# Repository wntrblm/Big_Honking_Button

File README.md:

# Winterbloom Big Honking Button

Winterbloom Big Honking Button is an open-source Eurorack module. You can find out more at https://honk.wntr.dev/.

## License and contributing

The code here is available under the [MIT License](firmware/LICENSE), the hardware designs are available under [CC BY-SA 4.0](hardware/LICENSE). I welcome contributors, please read the [Code of Conduct](CODE_OF_CONDUCT.md) first. :)

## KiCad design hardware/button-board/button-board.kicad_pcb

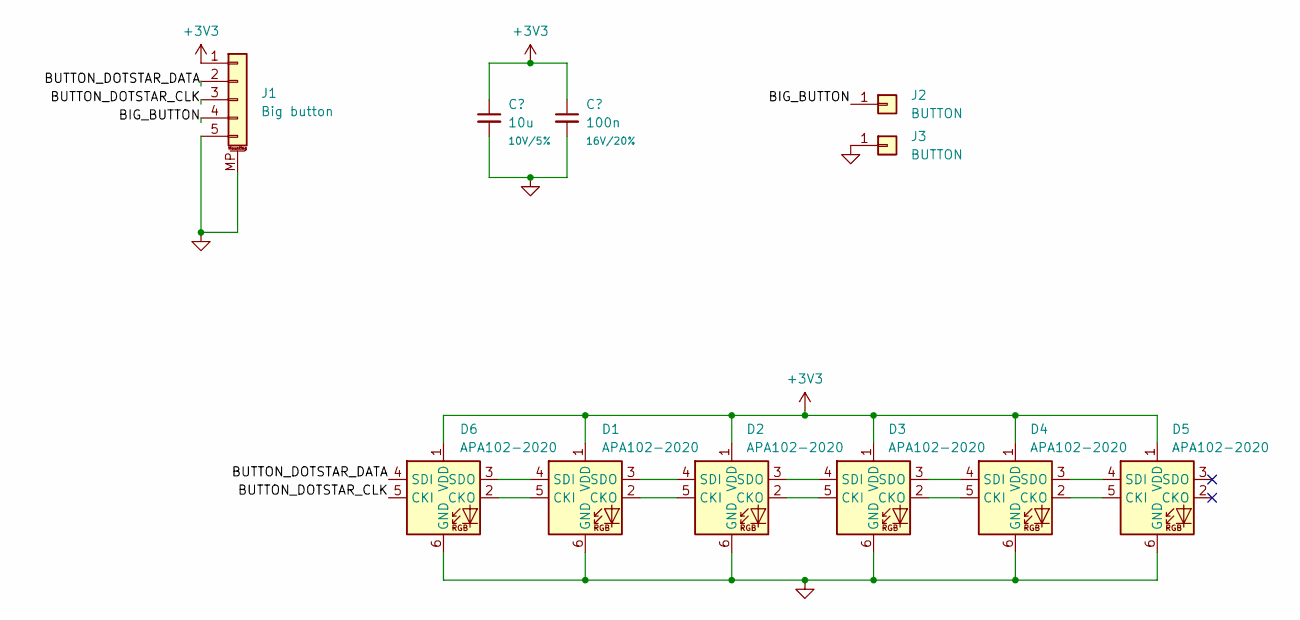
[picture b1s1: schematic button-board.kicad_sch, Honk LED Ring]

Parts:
C1: 10u; C_0603_HandSolder; Rating 10V/5%; MPN CL10A106MP8NNNC
C2: 100n; C_0603_HandSolder; Rating 16V/20%; MPN CL05B104KO5NNNC
D1, D2, D3, D4, D5, D6: APA102-2020; LED-APA102-2020; MPN APA102-2020
J1: Big button; JST_SH_SM05B-SRSS-TB_1x05-1MP_P1.00mm_Horizontal
J2, J3: BUTTON; SolderWire-0.75sqmm_1x01_D1.25mm_OD2.3mm

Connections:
+3V3: C1.1, C2.1, D1.1 (VDD), D2.1 (VDD), D3.1 (VDD), D4.1 (VDD), D5.1 (VDD), D6.1 (VDD), J1.1
/BIG_BUTTON: J1.4, J2.1
/BUTTON_DOTSTAR_CLK: D6.5 (CKI), J1.3
/BUTTON_DOTSTAR_DATA: D6.4 (SDI), J1.2
GND: C1.2, C2.2, D1.6 (GND), D2.6 (GND), D3.6 (GND), D4.6 (GND), D5.6 (GND), D6.6 (GND), J1.5, J1.MP (MountPin), J3.1
unnamed: D1.5 (CKI), D6.2 (CKO)
unnamed: D1.2 (CKO), D2.5 (CKI)
unnamed: D1.4 (SDI), D6.3 (SDO)
unnamed: D1.3 (SDO), D2.4 (SDI)
unnamed: D2.2 (CKO), D3.5 (CKI)
unnamed: D2.3 (SDO), D3.4 (SDI)
unnamed: D3.2 (CKO), D4.5 (CKI)
unnamed: D3.3 (SDO), D4.4 (SDI)
unnamed: D4.2 (CKO), D5.5 (CKI)
unnamed: D4.3 (SDO), D5.4 (SDI)

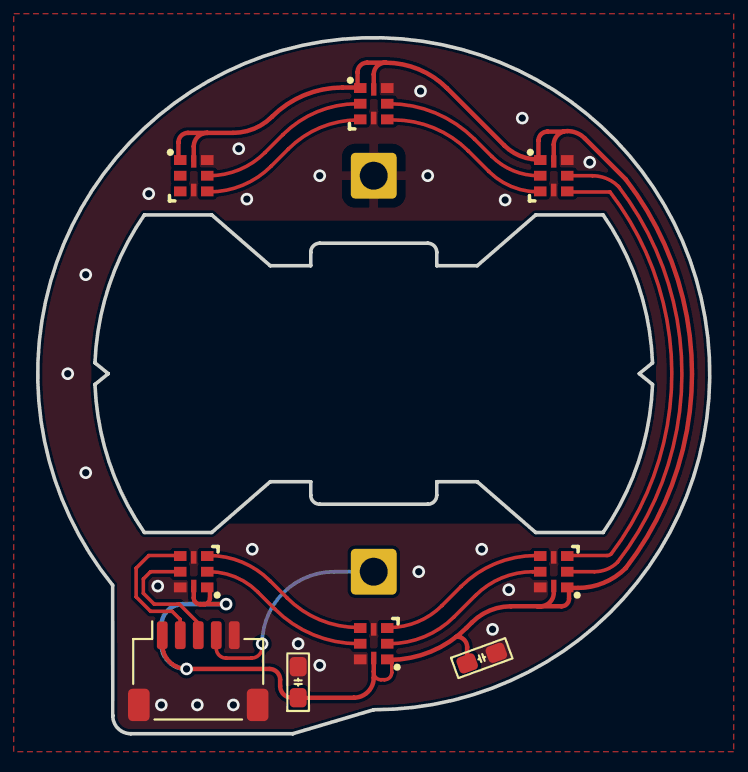
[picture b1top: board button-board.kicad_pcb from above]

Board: 2 copper layers, 37.3 x 38.7 mm, 11 parts (0 on the bottom side), 15 nets.

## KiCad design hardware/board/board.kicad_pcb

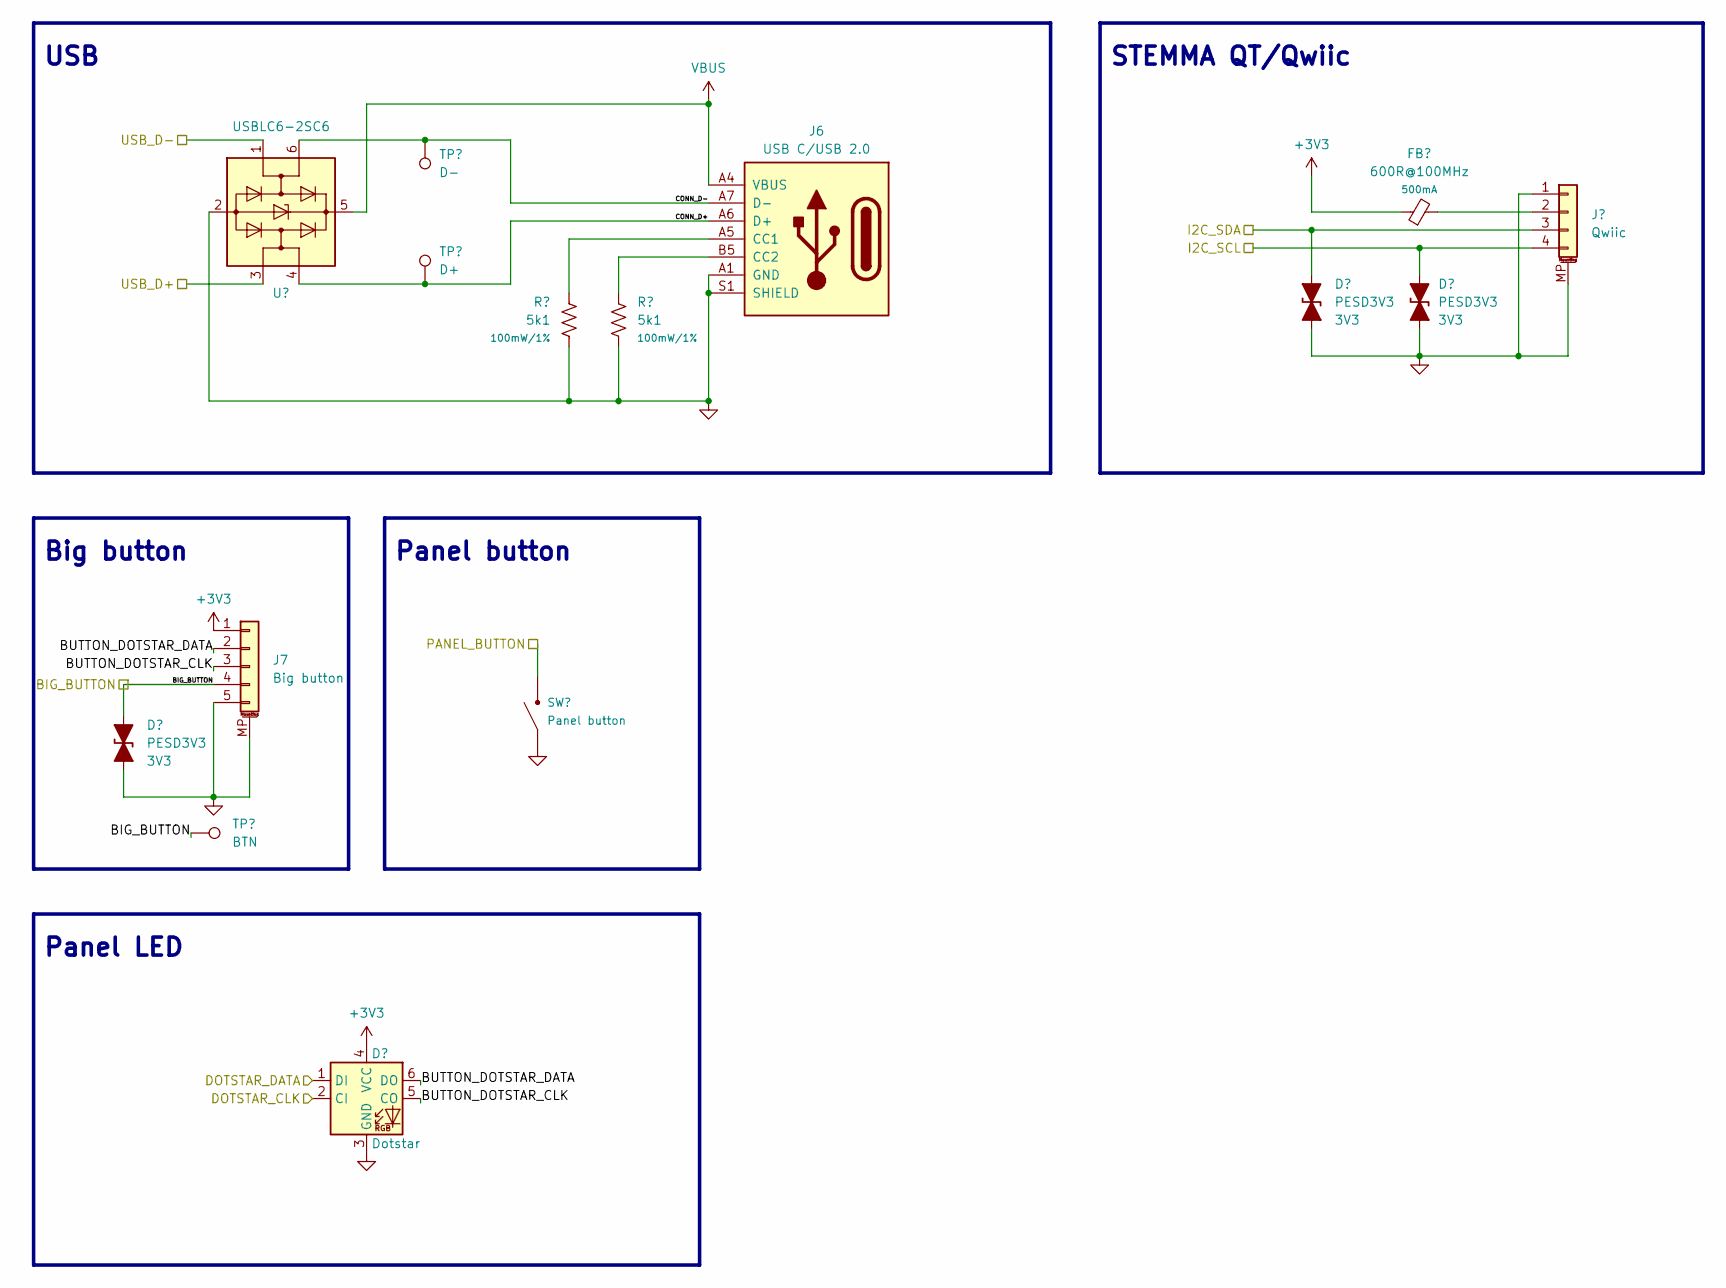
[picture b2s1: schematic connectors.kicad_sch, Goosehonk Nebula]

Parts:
D6: Dotstar; LED_APA102_Dotstar_5050; MPN SK9822
D7, D8, D9: PESD3V3; D_SOD-323; Rating 3V3; mpn PESD3V3L1BA,115
FB4: 600R@100MHz; L_0603_HandSolder; Rating 500mA; MPN 742792651
J6: USB C/USB 2.0; USB_C_Vertical_GT-USB-7038X; MPN GT-USB-7038D, MC-110LD-L124, GT-USB-703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
J7: Big button; JST_SH_SM05B-SRSS-TB_1x05-1MP_P1.00mm_Horizontal
J9: Qwiic; JST_SH_SM04B-SRSS-TB_1x04-1MP_P1.00mm_Horizontal
R23, R24: 5k1; R_0603_HandSolder; Rating 100mW/1%; MPN ERJ-2RKF2201X
SW2: Panel button; Tactile_Switch_6mm; MPN TL1105SPF160Q, TL1105SPF100Q, TL1105SPF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
TP15: D-; TestPoint_Pad_D1.0mm
TP16: D+; TestPoint_Pad_D1.0mm
TP17: BTN; TestPoint_Pad_D1.0mm
U7: USBLC6-2SC6; SOT-23-6; MPN USBLC6-2SC6, SRL05-TP

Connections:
+3V3: D6.4 (VCC), FB4.1, J7.1; also elsewhere on the board
/Connectors & buttons/BIG_BUTTON: D9.2 (A2), J7.4, TP17.1; also elsewhere on the board
/Connectors & buttons/BUTTON_DOTSTAR_CLK: D6.5 (CO), J7.3
/Connectors & buttons/BUTTON_DOTSTAR_DATA: D6.6 (DO), J7.2
/Connectors & buttons/CONN_D+: J6.A6 (D+), J6.B6 (D+), TP16.1, U7.4 (I/O2)
/Connectors & buttons/CONN_D-: J6.A7 (D-), J6.B7 (D-), TP15.1, U7.6 (I/O1)
/Connectors & buttons/DOTSTAR_CLK: D6.2 (CI); also elsewhere on the board
/Connectors & buttons/DOTSTAR_DATA: D6.1 (DI); also elsewhere on the board
/Connectors & buttons/PANEL_BUTTON: SW2.2; also elsewhere on the board
/Connectors & buttons/USB_D+: U7.3 (I/O2); also elsewhere on the board
/Connectors & buttons/USB_D-: U7.1 (I/O1); also elsewhere on the board
/MCU/I2C_SCL: D8.2 (A2), J9.4; also elsewhere on the board
/MCU/I2C_SDA: D7.2 (A2), J9.3; also elsewhere on the board
GND: D6.3 (GND), D7.1 (A1), D8.1 (A1), D9.1 (A1), J6.A1 (GND), J6.A12 (GND), J6.B1 (GND), J6.B12 (GND), J6.S1 (SHIELD), J7.5, J7.MP (MountPin), J9.1, J9.MP (MountPin), R23.2, R24.2, SW2.1, U7.2 (GND); also elsewhere on the board
unnamed: J6.A5 (CC1), R23.1
unnamed: J6.B5 (CC2), R24.1
unnamed: FB4.2, J9.2
VBUS: J6.A4 (VBUS), J6.A9 (VBUS), J6.B4 (VBUS), J6.B9 (VBUS), U7.5 (VBUS); also elsewhere on the board

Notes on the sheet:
USB
Panel button
Panel LED
STEMMA QT/Qwiic
Big button

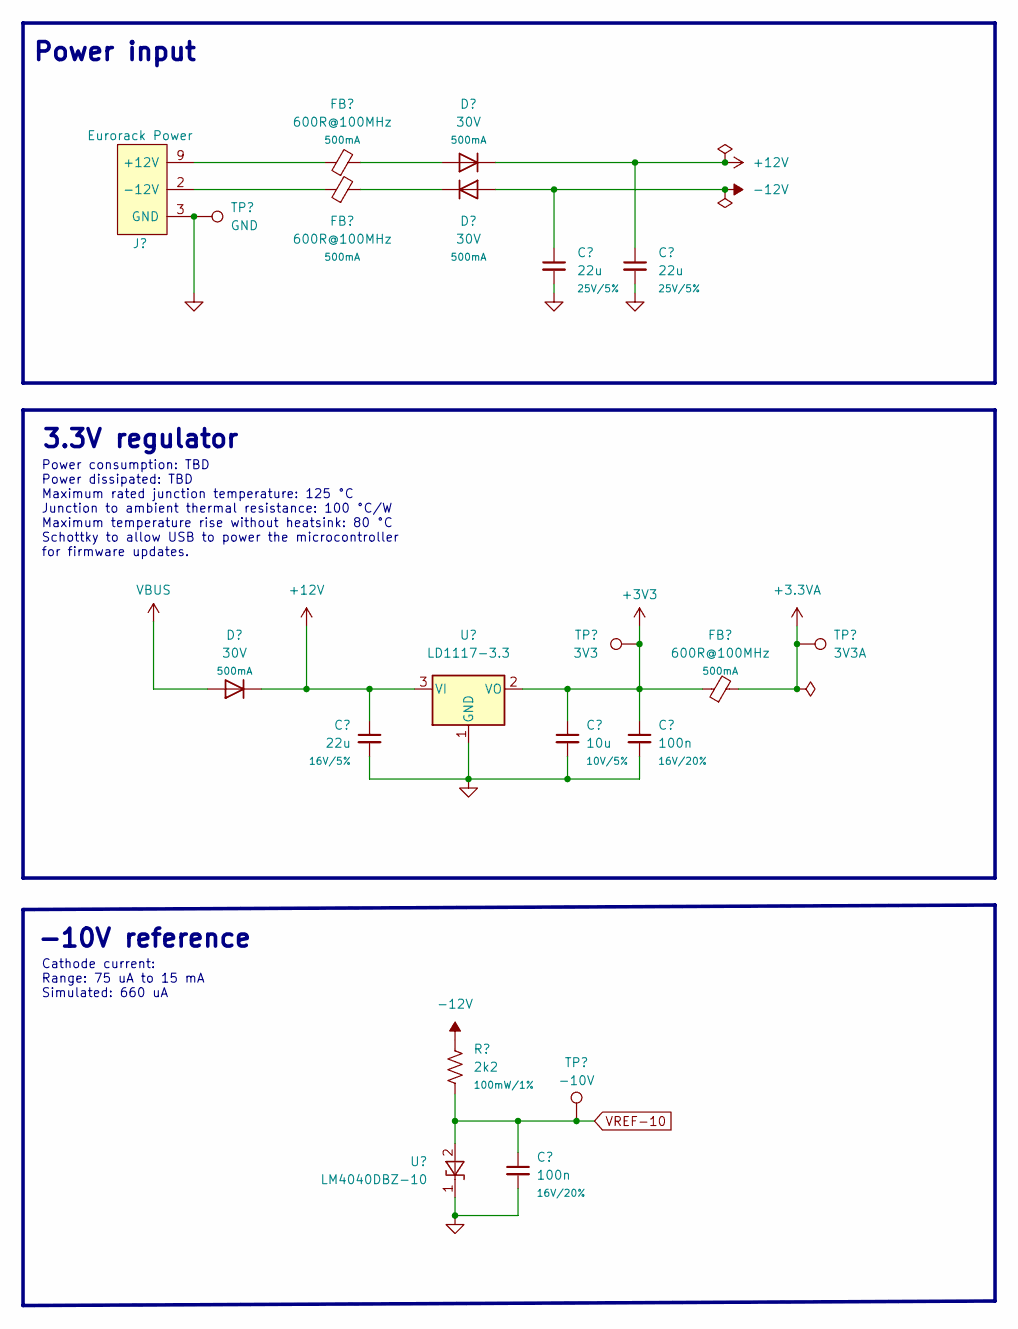
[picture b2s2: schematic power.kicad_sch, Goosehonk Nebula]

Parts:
C1, C2: 22u; C_0805_HandSolder; Rating 25V/5%; MPN CL21A226MAYNNNE
C5: 22u; C_0805_HandSolder; Rating 16V/5%; MPN CL21A226MAYNNNE
C6: 10u; C_0603_HandSolder; Rating 10V/5%; MPN CL10A106MP8NNNC
C7, C8: 100n; C_0603_HandSolder; Rating 16V/20%; MPN CL05B104KO5NNNC
D1, D2, D3: 30V; D_SOD-123; Rating 500mA; MPN PMEG2005EGWJ, PMEG3005EGWX
FB1, FB2, FB3: 600R@100MHz; L_0603_HandSolder; Rating 500mA; MPN 742792651
J1: Eurorack Power; Eurorack_Power_2x5_Shrouded_Lock; MPN 4UCONN 20253, On-shore 302-S101
R1: 2k2; R_0603_HandSolder; Rating 100mW/1%; MPN ERJ-2RKF2201X
TP1: GND; TestPoint_Pad_D1.0mm
TP2: 3V3; TestPoint_Pad_D1.0mm
TP3: 3V3A; TestPoint_Pad_D1.0mm
TP4: -10V; TestPoint_Pad_D1.0mm
U1: LD1117-3.3; TO-252-3_TabPin2; MPN LD1117DT33TR, AZ1117CD-3.3TRG1
U2: LM4040DBZ-10; SOT-23; MPN LM4040DIM3-10.0/NOPB

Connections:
+3.3VA: FB3.2, TP3.1; also elsewhere on the board
+3V3: C6.1, C7.1, FB3.1, TP2.1, U1.2 (VO); also elsewhere on the board
+12V: C2.1, C5.1, D1.1 (K), D3.1 (K), U1.3 (VI); also elsewhere on the board
-12V: C1.1, D2.2 (A), R1.1; also elsewhere on the board
GND: C1.2, C2.2, C5.2, C6.2, C7.2, C8.2, J1.3 (GND), J1.4 (GND), J1.5 (GND), J1.6 (GND), J1.7 (GND), J1.8 (GND), TP1.1, U1.1 (GND), U2.1 (K); also elsewhere on the board
unnamed: D1.2 (A), FB1.2
unnamed: D2.1 (K), FB2.2
unnamed: FB1.1, J1.9 (+12V), J1.10 (+12V)
unnamed: FB2.1, J1.1 (-12V), J1.2 (-12V)
VBUS: D3.2 (A); also elsewhere on the board
VREF-10: C8.1, R1.2, TP4.1, U2.2 (A); also elsewhere on the board

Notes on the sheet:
-10V reference
Power consumption: TBD Power dissipated: TBD Maximum rated junction temperature: 125 °C Junction to ambient thermal resistance: 100 °C/W Maximum temperature rise without heatsink: 80 °C Schottky to allow USB to power the microcontroller for firmware updates.
3.3V regulator
Cathode current: Range: 75 uA to 15 mA Simulated: 660 uA
Power input

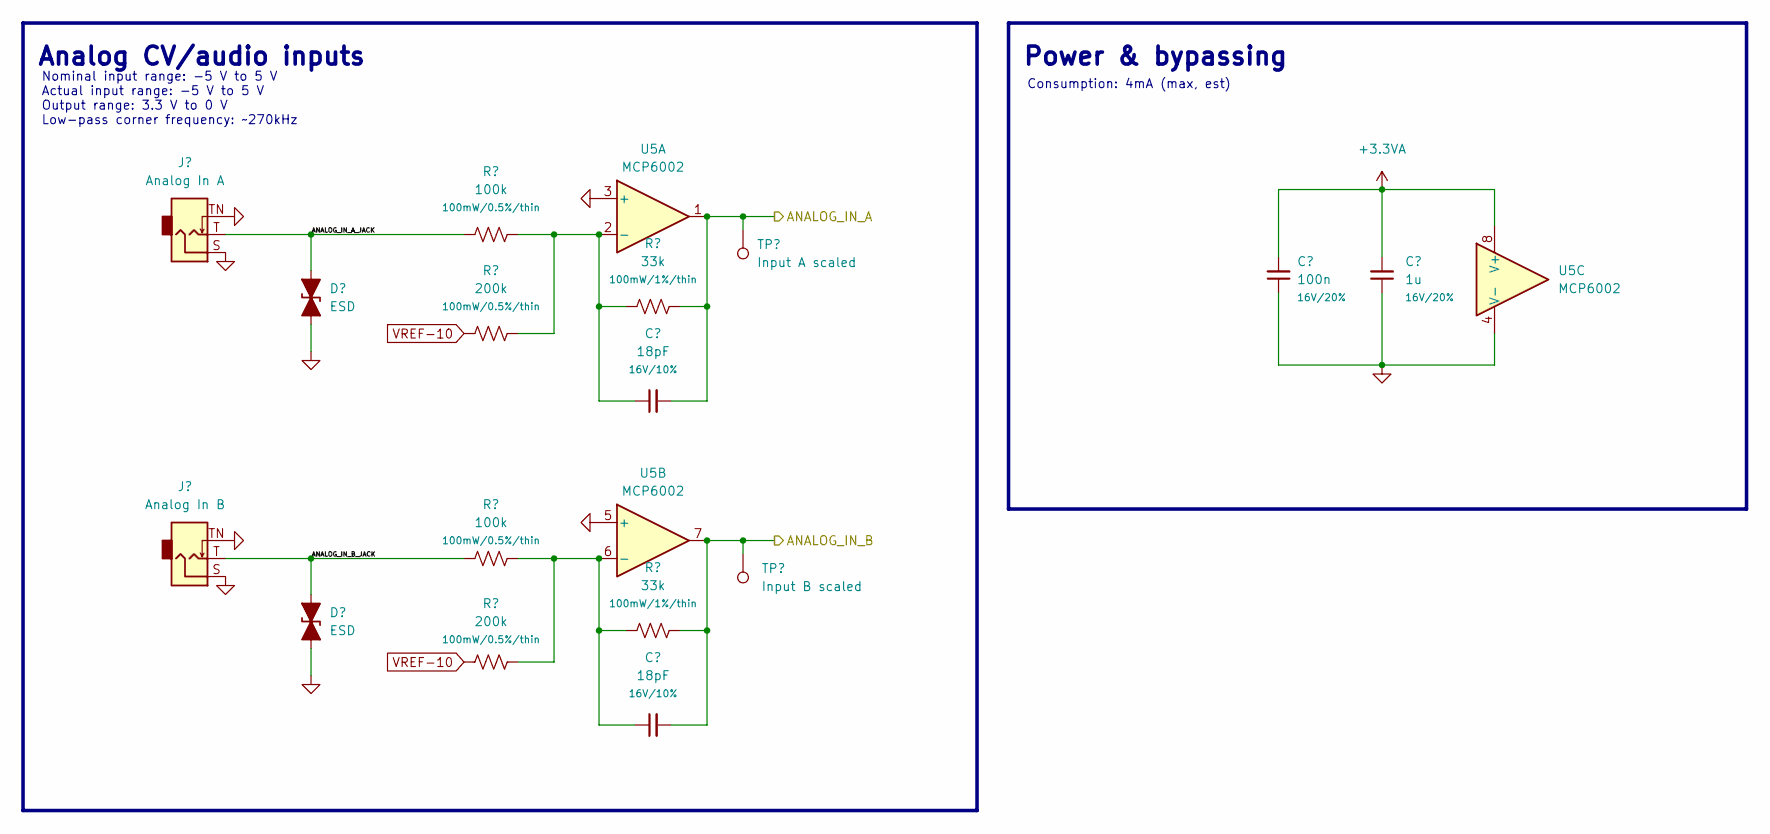
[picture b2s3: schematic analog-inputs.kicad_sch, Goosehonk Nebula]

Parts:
C16, C17: 18pF; C_0603_HandSolder; Rating 16V/10%; MPN GRM155R71H222KA01D
C18: 100n; C_0603_HandSolder; Rating 16V/20%; MPN CL05B104KO5NNNC
C19: 1u; C_0603_HandSolder; Rating 16V/20%; MPN CL05A105KO5NNNC
D4, D5: ESD; C_0603_HandSolder; Rating 20V+; MPN B72500T0250K060
J2: Analog In A; AudioJack_WQP518MA; MPN WQP-WQP518MA
J3: Analog In B; AudioJack_WQP518MA; MPN WQP-WQP518MA
R5, R8: 100k; R_0603_HandSolder; Rating 100mW/0.5%/thin; MPN RC0402DR-07100KL
R6, R9: 200k; R_0603_HandSolder; Rating 100mW/0.5%/thin; MPN RP73PF1E196KBTD, RK73H1ETTP1963F
R7, R10: 33k; R_0603_HandSolder; Rating 100mW/1%/thin; MPN RT0402BRD0761K9L, ERA-2AEB6192X
TP10: Input A scaled; TestPoint_Pad_D1.0mm
TP11: Input B scaled; TestPoint_Pad_D1.0mm
U5: MCP6002; MSOP-8_3x3mm_P0.65mm; MPN MCP6002T-I/MS, MCP6002-I/MS, MCP6002T-E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

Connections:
+3.3VA: C18.2, C19.2, U5.8 (V+); also elsewhere on the board
/Analog Inputs/ANALOG_IN_A: C16.2, R7.1, TP10.1, U5.1; also elsewhere on the board
/Analog Inputs/ANALOG_IN_A_JACK: D4.2 (A2), J2.T (Tip), R5.2
/Analog Inputs/ANALOG_IN_B: C17.2, R10.1, TP11.1, U5.7; also elsewhere on the board
/Analog Inputs/ANALOG_IN_B_JACK: D5.2 (A2), J3.T (Tip), R8.2
GND: C18.1, C19.1, D4.1 (A1), D5.1 (A1), J2.S (Sleeve), J2.TN (Tip_normalize), J3.S (Sleeve), J3.TN (Tip_normalize), U5.3 (+), U5.4 (V-), U5.5 (+); also elsewhere on the board
unnamed: C16.1, R5.1, R6.1, R7.2, U5.2 (-)
unnamed: C17.1, R8.1, R9.1, R10.2, U5.6 (-)
VREF-10: R6.2, R9.2; also elsewhere on the board

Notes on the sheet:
Nominal input range: -5 V to 5 V Actual input range: -5 V to 5 V Output range: 3.3 V to 0 V Low-pass corner frequency: ~270kHz
Consumption: 4mA (max, est)
Analog CV/audio inputs
Power & bypassing

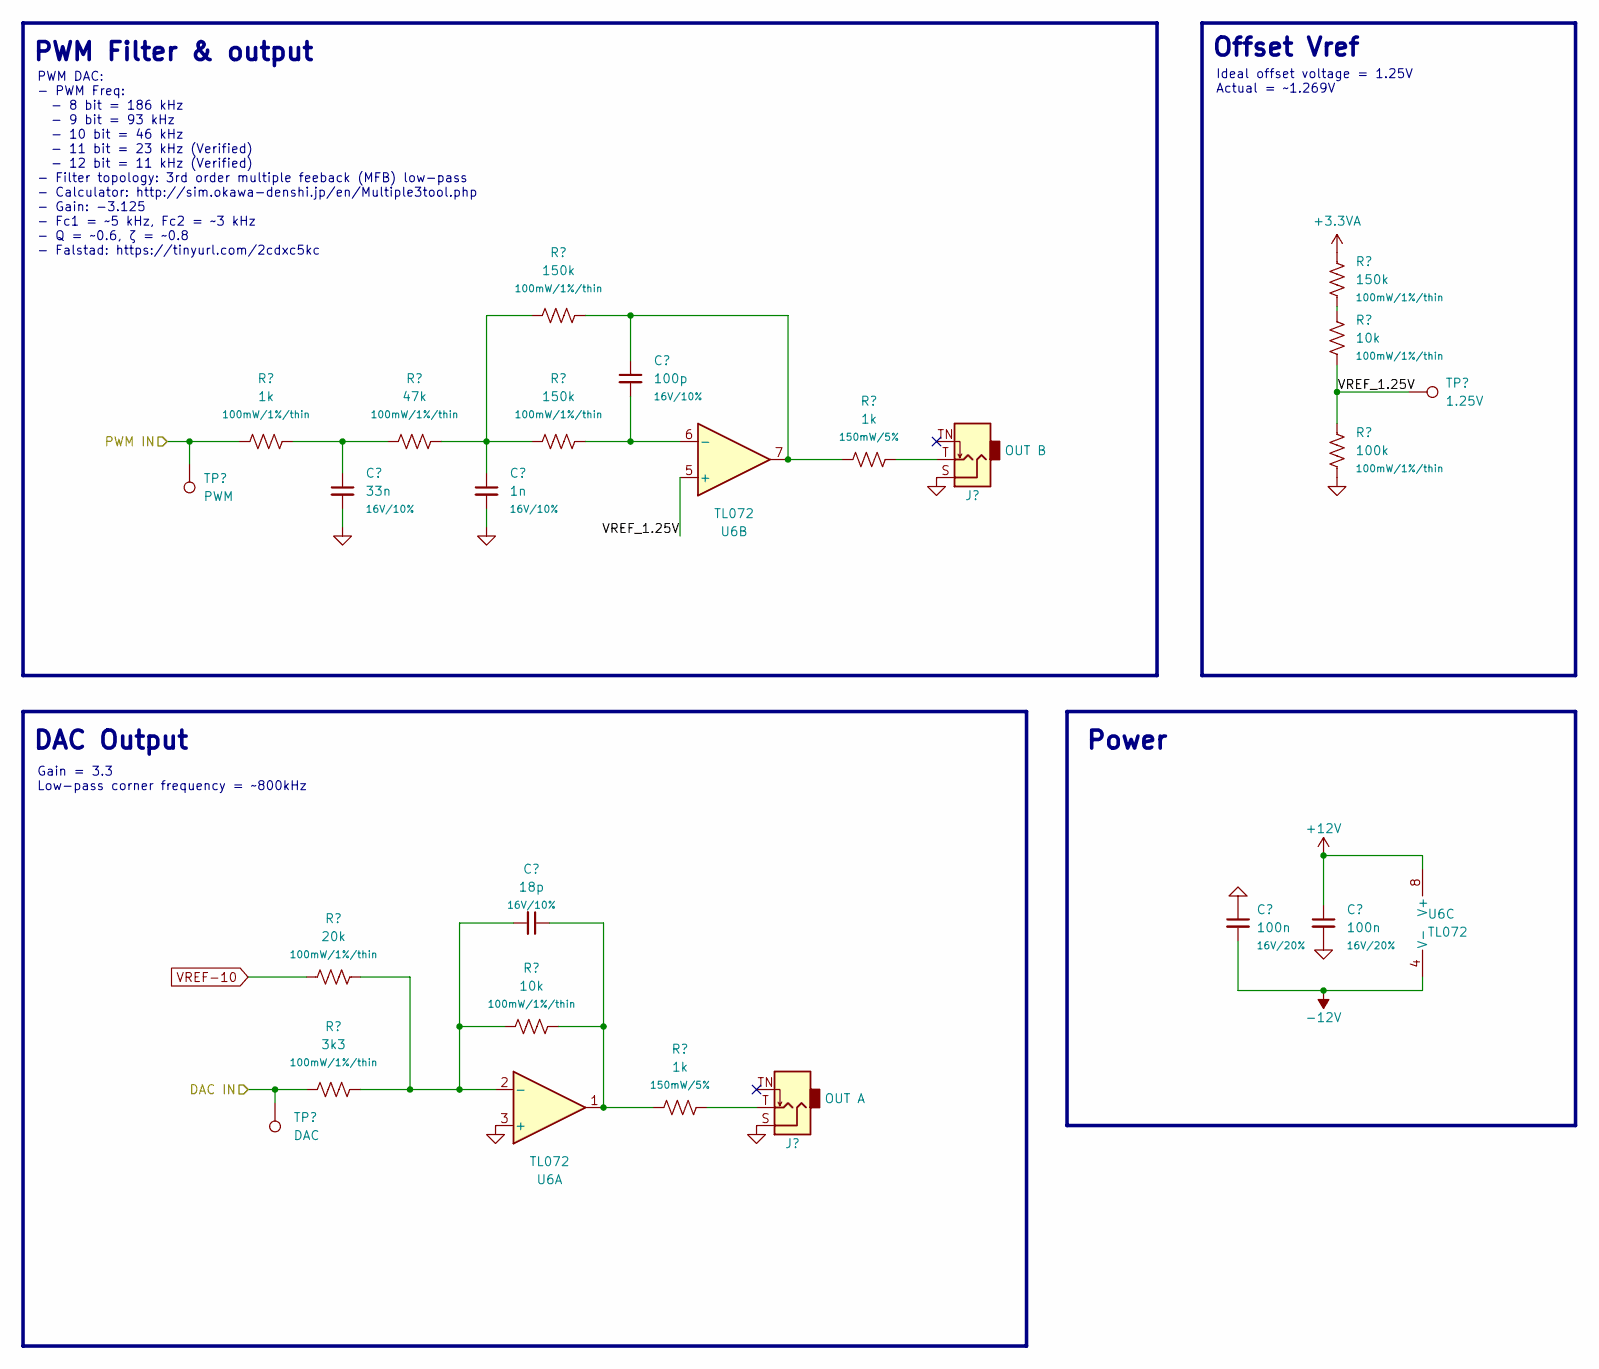
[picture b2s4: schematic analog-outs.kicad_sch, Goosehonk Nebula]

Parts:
C20, C21: 100n; C_0603_HandSolder; Rating 16V/20%; MPN CL05B104KO5NNNC
C22: 18p; C_0603_HandSolder; Rating 16V/10%; MPN CL05C180JB5NNNC
C23: 33n; C_0603_HandSolder; Rating 16V/10%; MPN CL05C180JB5NNNC
C24: 1n; C_0603_HandSolder; Rating 16V/10%; MPN CL05C180JB5NNNC
C25: 100p; C_0603_HandSolder; Rating 16V/10%; MPN CL05C180JB5NNNC
J4: OUT A; AudioJack_WQP518MA; MPN WQP-WQP518MA
J5: OUT B; AudioJack_WQP518MA; MPN WQP-WQP518MA
R11: 20k; R_0603_HandSolder; Rating 100mW/1%/thin; MPN RC0402DR-07100KL
R12: 3k3; R_0603_HandSolder; Rating 100mW/1%/thin; MPN RC0402DR-07100KL
R13, R21: 10k; R_0603_HandSolder; Rating 100mW/1%/thin; MPN RC0402DR-07100KL
R14, R19: 1k; R_0603_HandSolder; Rating 150mW/5%; MPN MCT06030C1001FP500, ERA-3AEB102V
R15: 1k; R_0603_HandSolder; Rating 100mW/1%/thin; MPN RC0402DR-07100KL
R16: 47k; R_0603_HandSolder; Rating 100mW/1%/thin; MPN RC0402DR-07100KL
R17, R18, R20: 150k; R_0603_HandSolder; Rating 100mW/1%/thin; MPN RC0402DR-07100KL
R22: 100k; R_0603_HandSolder; Rating 100mW/1%/thin; MPN RC0402DR-07100KL
TP12: DAC; TestPoint_Pad_D1.0mm
TP13: PWM; TestPoint_Pad_D1.0mm
TP14: 1.25V; TestPoint_Pad_D1.0mm
U6: TL072; TSSOP-8_4.4x3mm_P0.65mm

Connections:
+3.3VA: R20.1; also elsewhere on the board
+12V: C21.1, U6.8 (V+); also elsewhere on the board
-12V: C20.2, U6.4 (V-); also elsewhere on the board
/Analog Outs/DAC IN: R12.2, TP12.1; also elsewhere on the board
/Analog Outs/PWM IN: R15.2, TP13.1; also elsewhere on the board
/Analog Outs/VREF_1.25V: R21.2, R22.1, TP14.1, U6.5 (+)
GND: C20.1, C21.2, C23.2, C24.2, J4.S (Sleeve), J5.S (Sleeve), R22.2, U6.3 (+); also elsewhere on the board
unnamed: C22.1, R13.1, R14.1, U6.1
unnamed: C23.1, R15.1, R16.2
unnamed: C24.1, R16.1, R17.2, R18.2
unnamed: C25.1, R17.1, R19.1, U6.7
unnamed: J4.T (Tip), R14.2
unnamed: J5.T (Tip), R19.2
unnamed: R20.2, R21.1
unnamed: C22.2, R11.1, R12.1, R13.2, U6.2 (-)
unnamed: C25.2, R18.1, U6.6 (-)
VREF-10: R11.2; also elsewhere on the board

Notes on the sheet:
Ideal offset voltage = 1.25V Actual = ~1.269V
Gain = 3.3 Low-pass corner frequency = ~800kHz
Offset Vref
PWM Filter & output
DAC Output
Power
PWM DAC: - PWM Freq: - 8 bit = 186 kHz - 9 bit = 93 kHz - 10 bit = 46 kHz - 11 bit = 23 kHz (Verified) - 12 bit = 11 kHz (Verified) - Filter topology: 3rd order multiple feeback (MFB) low-pass - Calculator: http://sim.okawa-denshi.jp/en/Multiple3tool.php - Gain: -3.125 - Fc1 = ~5 kHz, Fc2 = ~3 kHz 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

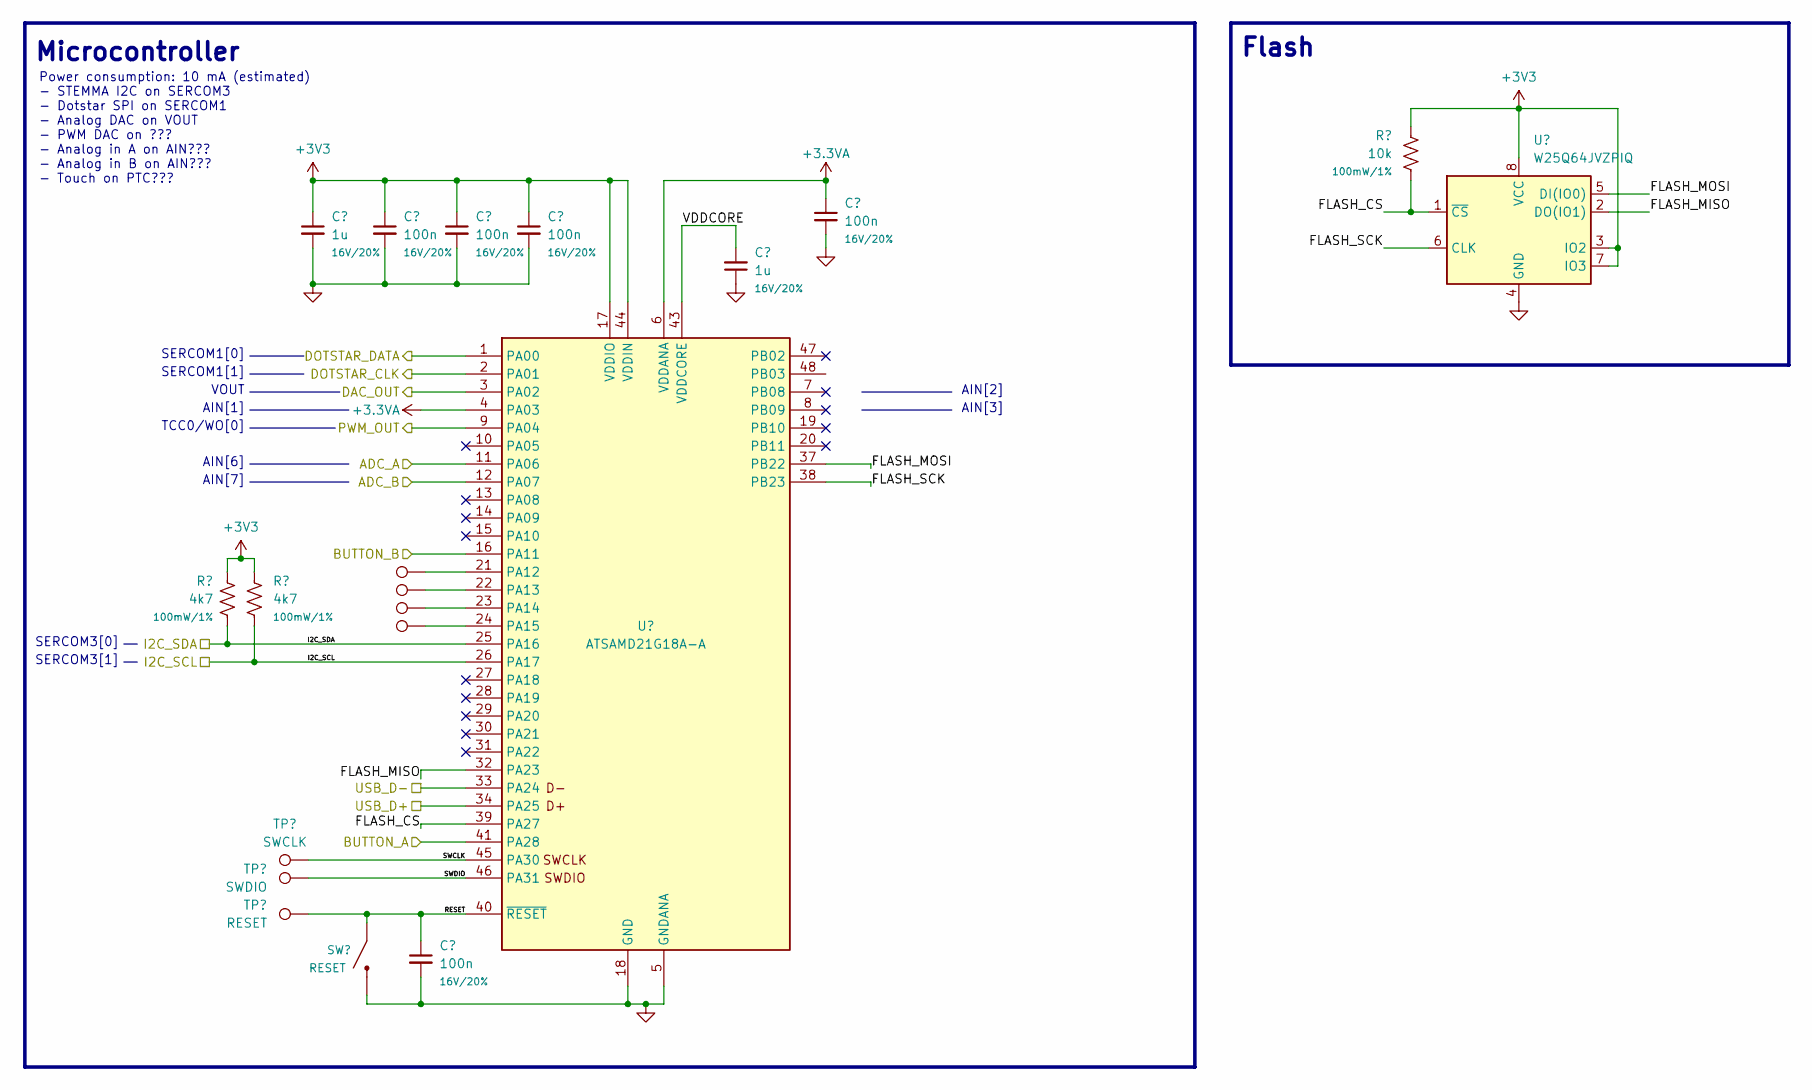
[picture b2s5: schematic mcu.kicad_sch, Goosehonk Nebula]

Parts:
C9, C14: 1u; C_0603_HandSolder; Rating 16V/20%; MPN CL05A105KO5NNNC
C10, C11, C12, C13, C15: 100n; C_0603_HandSolder; Rating 16V/20%; MPN CL05B104KO5NNNC
R2, R3: 4k7; R_0603_HandSolder; Rating 100mW/1%
R4: 10k; R_0603_HandSolder; Rating 100mW/1%; MPN ERJ-2RKF2201X
SW1: RESET; Tactile_Switch_4.2mm; MPN PTS815 SJM 250 SMTR LFS
TP7: SWCLK; TestPoint_Pad_D1.0mm
TP8: SWDIO; TestPoint_Pad_D1.0mm
TP9: RESET; TestPoint_Pad_D1.0mm
TP18: PA12; TestPoint_Pad_D1.0mm
TP19, TP20: PA13; TestPoint_Pad_D1.0mm
TP21: PA15; TestPoint_Pad_D1.0mm
U3: ATSAMD21G18A-A; TQFP-48_7x7mm_P0.5mm; MPN ATSAMD21G18A-A
U4: W25Q64JVZPIQ; WSON-8-1EP_6x5mm_P1.27mm_EP3.4x4mm; mpn W25Q64JVZPIQ

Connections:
+3.3VA: C15.1, U3.4 (PA03), U3.6 (VDDANA); also elsewhere on the board
+3V3: C9.1, C10.1, C12.1, C13.1, R2.1, R3.1, R4.1, U3.17 (VDDIO), U3.36 (VDDIO), U3.44 (VDDIN), U4.3 (IO2), U4.7 (IO3), U4.8 (VCC); also elsewhere on the board
/Analog Inputs/ANALOG_IN_A: U3.11 (PA06); also elsewhere on the board
/Analog Inputs/ANALOG_IN_B: U3.12 (PA07); also elsewhere on the board
/Analog Outs/DAC IN: U3.3 (PA02); also elsewhere on the board
/Analog Outs/PWM IN: U3.9 (PA04); also elsewhere on the board
/Connectors & buttons/BIG_BUTTON: U3.41 (PA28); also elsewhere on the board
/Connectors & buttons/DOTSTAR_CLK: U3.2 (PA01); also elsewhere on the board
/Connectors & buttons/DOTSTAR_DATA: U3.1 (PA00); also elsewhere on the board
/Connectors & buttons/PANEL_BUTTON: U3.16 (PA11); also elsewhere on the board
/Connectors & buttons/USB_D+: U3.34 (PA25); also elsewhere on the board
/Connectors & buttons/USB_D-: U3.33 (PA24); also elsewhere on the board
/MCU/FLASH_CS: R4.2, U3.39 (PA27), U4.1 (~CS)
/MCU/FLASH_MISO: U3.32 (PA23), U4.2 (DO(IO1))
/MCU/FLASH_MOSI: U3.37 (PB22), U4.5 (DI(IO0))
/MCU/FLASH_SCK: U3.38 (PB23), U4.6 (CLK)
/MCU/I2C_SCL: R3.2, U3.26 (PA17); also elsewhere on the board
/MCU/I2C_SDA: R2.2, U3.25 (PA16); also elsewhere on the board
/MCU/RESET: C11.1, SW1.1, TP9.1, U3.40 (~RESET)
/MCU/SWCLK: TP7.1, U3.45 (PA30)
/MCU/SWDIO: TP8.1, U3.46 (PA31)
/MCU/VDDCORE: C14.2, U3.43 (VDDCORE)
GND: C9.2, C10.2, C11.2, C12.2, C13.2, C14.1, C15.2, SW1.2, U3.5 (GNDANA), U3.18 (GND), U3.35 (GND), U3.42 (GND), U4.4 (GND); also elsewhere on the board
unnamed: TP18.1, U3.21 (PA12)
unnamed: TP19.1, U3.22 (PA13)
unnamed: TP20.1, U3.23 (PA14)
unnamed: TP21.1, U3.24 (PA15)

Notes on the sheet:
Microcontroller
SERCOM3[0]
TCC0/WO[0]
SERCOM3[1]
SERCOM1[1]
AIN[7]
AIN[6]
AIN[3]
Power consumption: 10 mA (estimated) - STEMMA I2C on SERCOM3 - Dotstar SPI on SERCOM1 - Analog DAC on VOUT - PWM DAC on ??? - Analog in A on AIN??? - Analog in B on AIN??? - Touch on PTC???
AIN[2]
VOUT
AIN[1]
SERCOM1[0]
Flash

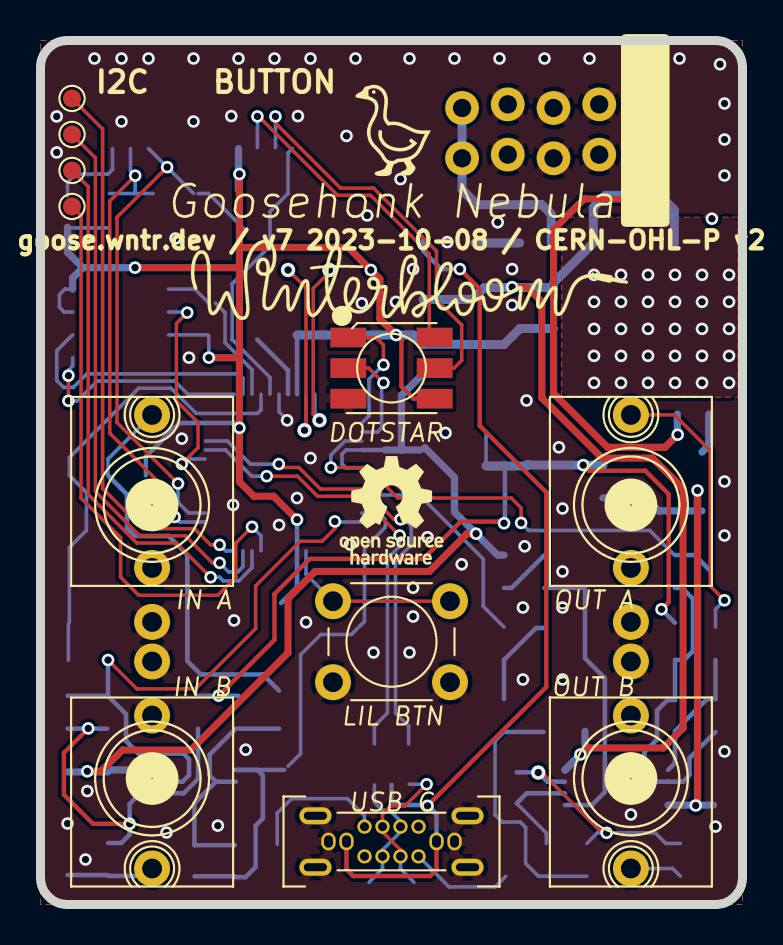
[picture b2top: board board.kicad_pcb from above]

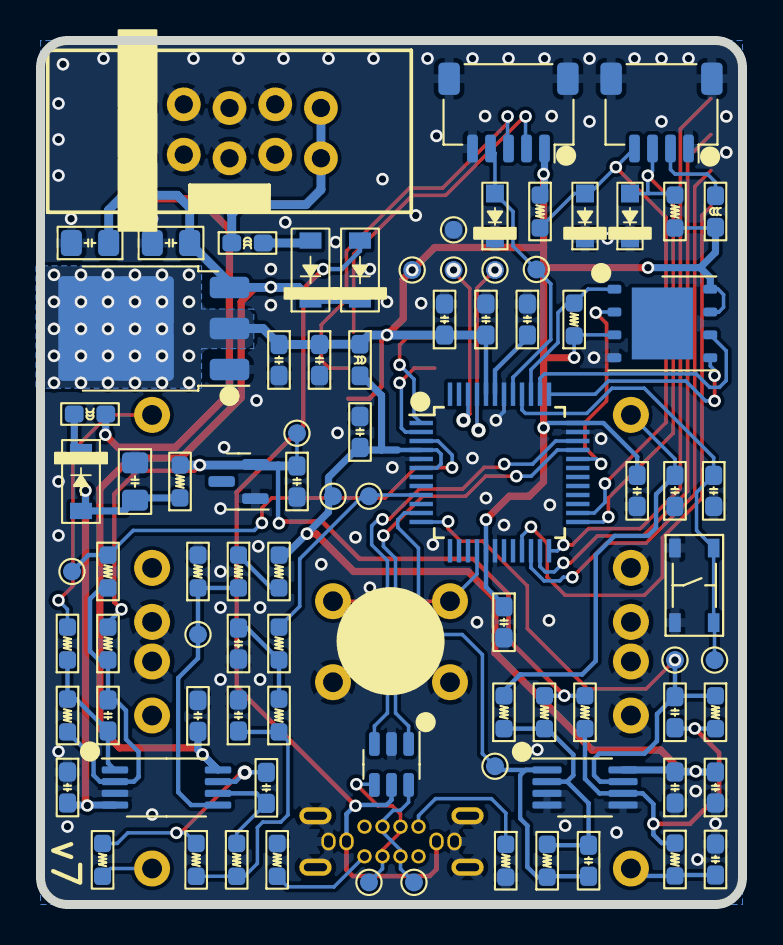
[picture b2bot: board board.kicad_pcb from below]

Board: 2 copper layers, 39.0 x 48.0 mm, 96 parts (85 on the bottom side), 56 nets.

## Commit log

2020-03-03 Add initial hardware design
2020-03-03 Add WIP panel design
2020-03-03 Add WIP firmware
2020-03-05 Fix incorrect resistor values
2020-03-05 Update panel
2020-03-20 Fix issues found in the first prototype
2020-03-22 Fix stroke property in panel reference
2020-04-10 Update panel with new logo
2020-04-24 Add firmware
2020-04-24 Make panel reversable
2020-04-24 Fix pinout on zener diode
2020-04-25 Add user guide
2020-04-25 Deployed b3a90c5 with MkDocs version: 1.1
2020-04-25 Create CNAME
2020-05-14 Update board
2020-05-14 Fix readme
2020-06-23 Add more samples, add examples, add ability to loop samples
2020-06-23 Add examples to the user guide
2020-06-23 Deployed c91add2 with MkDocs version: 1.1
2020-06-27 Add a burst generator example
2020-07-01 Fix link to random sample
2020-07-01 Deployed cc9208f with MkDocs version: 1.1
2020-07-18 Update docs to say 44.1kHz instead of 22kHz
    Hello! I just got this module (it's fantastic!), and uploaded to it the latest release, but as I was trying to load my own samples onto it, I found two things which seem to have drifted from these do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
    1. The sample that comes with it is called `honk.wav` and not `sample.wav` -- was an earlier version called `sample.wav`?
    2. The `honk.wav` audio file is 16-bit signed mono WAV at _44.1kHz_ and not 22kHz... I found this out the hard way because I kept loading my own samples at 22kHz and wondering why they were playing b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
2020-07-18 Update docs to say 44.1kHz instead of 22kHz (#3)
    Hello! I just got this module (it's fantastic!), and uploaded to it the latest release, but as I was trying to load my own samples onto it, I found two things which seem to have drifted from these do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
    1. The sample that comes with it is called `honk.wav` and not `sample.wav` -- was an earlier version called `sample.wav`?
    2. The `honk.wav` audio file is 16-bit signed mono WAV at _44.1kHz_ and not 22kHz... I found this out the hard way because I kept loading my own samples at 22kHz and wondering why they were playing b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
2020-07-26 Add a burst generator example (#2)
2020-09-29 Add first draft of DIY kit build guide.
2020-09-29 Deployed 3c4f7f7 with MkDocs version: 1.1.2
2020-09-30 Add build guide
2020-10-08 Board revision v5
    - Switch to 8mb flash
    - Switch all resistors to 0603
    - Change CV input to -5 to +5
2020-10-09 Remove gerbers
2020-10-10 Update user guide with new theme
2020-10-10 Deployed 346e97f with MkDocs version: 1.1.2
2020-10-10 Fix some small issues with the theme
2020-11-10 Use libwinter for factory setup
2020-11-19 Fix use of WaveFile to support CircuitPython 6.0
2020-11-19 Add distribution to gitignore
2020-12-12 Add PDF of the schematic and a pre-submit hook to make sure it doesn't go out of sync.
2020-12-12 Add open source information and links to the hardware and firmware sources
2020-12-12 Deployed fb30380 with MkDocs version: 1.1.2
2020-12-12 Move docs to shared theme
2020-12-12 Deployed a4b9b8a with MkDocs version: 1.1.2
2020-12-13 Add link to documentation in the readme
2021-01-08 Update docs for v5
2021-01-08 Deployed 6ebb66a with MkDocs version: 1.1.2
2021-01-08 Update firmware to support BHB v5
2021-01-14 Work around circuitpython file copying issue
2021-01-22 Add CNAME
2021-02-01 Add an example for making arbitrary long honks.
2021-02-13 user_guide: increase contrast, mark external links
2021-02-13 Deployed d6863b9 with MkDocs version: 1.1.2
2021-02-13 Fix bug where high pitch CV would cause the sample rate to be too high.
2021-02-13 Fix bug where high pitch CV would cause the sample rate to be too high. (#7)
2021-02-13 Switch factory setup script to use wintertools
2021-02-13 Fix factory setup publish
2021-04-14 user guide: add warranty information
2021-04-14 factory: fixup to work with newest wintertools
2021-04-14 Deployed e2f20d2 with MkDocs version: 1.1.2
2021-07-08 docs: Update URLs to the project repository, since it moved
2021-07-08 Deployed 2f10b77 with MkDocs version: 1.2.1
2021-07-08 firmware: Add select_from_list_using_cv helper
2021-07-08 examples: Add CV select example
2021-07-08 examples: Add CV select sample (#9)
    * Add files via upload
    * Update CV_select.py
    * firmware: Add select_from_list_using_cv helper
    * examples: Add CV select example
2021-07-08 Deployed f3ecbaa with MkDocs version: 1.2.1
2021-07-09 user guide: Use new images for the build guide, fixup small issues on the main user guide
2021-07-09 Deployed 7aca5e5 with MkDocs version: 1.2.1
2021-07-09 Grammar fixes
    2 tiny fixes:
    1. `its` -> `it's`, meaning "it is"
    1. `taught` (past tense of _teach_) -> `taut` (tightly drawn, tense) [link](https://www.dictionary.com/browse/taut)
2021-07-09 user guide: small grammar fixes (#10)
    2 tiny fixes:
    1. `its` -> `it's`, meaning "it is"
    1. `taught` (past tense of _teach_) -> `taut` (tightly drawn, tense) [link](https://www.dictionary.com/browse/taut)
2021-07-09 Deployed e2dcd91 with MkDocs version: 1.2.1
2021-07-22 firmware: Add the ability to track pressed (triggered) and released for gate in and the button independently.
    Note: This is a *breaking* change. `bhb.update()` must be called for every loop in `code.py`.
    To upgrade, just replace:
    ```
    while True:
    ```
    with
2021-07-22 user guide: Update samples list
2021-07-22 user guide: Add code reference section
2021-07-22 factory: Setup release script
2021-07-22 Deployed bf7aa13 with MkDocs version: 1.2.1
2021-08-13 firmware: Fix off-by-one error in select_from_list_using_cv
2021-09-06 factory: Fix path to bootloader for JLink
2021-09-13 user guide: Fix example that used `winterbloom.BigHonkingButton` instead of `winterbloom_bhb.BigHonkingButton`
2021-09-13 Deployed 5169234 with MkDocs version: 1.2.1
2021-10-16 Factory: reset microcontroller after programming
2021-11-06 Deployed 4087e3e with MkDocs version: 1.2.3
2022-01-02 added long hong code and samples
2022-01-14 added long hong code and samples (#11)
2022-02-03 meta: automatically publish user guide when changes are pushed
2022-05-19 Switch to KiCAD 6
2022-10-03 Update URL to match what's working
2022-10-03 Update URL to match what's working (#12)
2022-11-18 Create silent_cycle.py
    Cycle silently though your samples (all samples in /sample directory) with the honking button and play them with the trigger input.
2022-11-18 Create silent_cycle.py (#13)
    Cycle silently though your samples (all samples in /sample directory) with the honking button and play them with the trigger input.
2023-08-17 hardware: Add initial version of honk2's mainboard and button board
2023-09-23 hardware: ignore *-backup directories
2023-09-23 hardware: change USB connector, change flash chip, change SPI flash pin assignments, other small updates to routing
2023-09-24 hardware: Revise button board- move all components to front side, update footprint for LEDs, add caps, change friction tabs to avoid interference with switch locking tabs
2023-10-09 hardware: rename to Goosehonk Nebula, prep v7
2023-10-13 hardware: refill zones and plot gerbers
2024-02-16 hardware: remove backups
2024-02-16 meta: cleaning up repo
2025-01-30 kicad updates
2025-01-30 Hardware: added faceplate

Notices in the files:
hardware/board/analog-inputs.kicad_sch:
CERN-OHL-P V2
